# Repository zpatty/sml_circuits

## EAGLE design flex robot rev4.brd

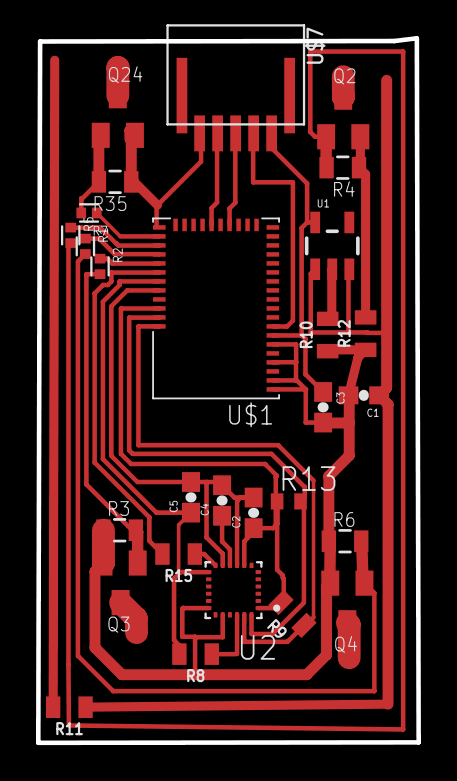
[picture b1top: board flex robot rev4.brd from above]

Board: 2 copper layers, 21.1 x 39.1 mm, 28 parts (0 on the bottom side), 25 nets.

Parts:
C1, C2, C4, C5: 1; 0603-CAP
C3: 0603-CAP
Q2, Q3, Q4, Q24: AO3400A; SOT23
R1, R2, R5, R7: ERA-2AED102X; RESC1005X40
R3, R4, R6, R35: 22.5kΩ; 0805
R8, R9, R10, R11, R12, R15: 0.22; 0805
R13: R0402
U1: TC7SU04F; SOT23-5
U2: MPU-9250; QFN40P300X300X105-25N
U$1: RFD77101
U$7: CON_01X05; HFW6R-2STE1LF

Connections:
GND: C1.2, C3.2, Q3.2, Q4.2, Q24.2, R3.1, R6.1, R10.1, R12.1, R35.1, U2.18, U2.20, U$1.1, U$1.2, U$1.4, U$1.6, U$1.19, U$1.30, U$7.5
unnamed: U$1.8, U$7.2
unnamed: C1.1, R11.1, U1.1, U1.3
unnamed: R1.1, U$1.33
unnamed: Q3.1, R2.2, R3.2
unnamed: U$1.23, U$7.3
unnamed: C4.1, U2.10
unnamed: U$1.25, U$7.4
unnamed: C2.2, C4.2, C5.2, U2.9, U2.11, U$1.37
unnamed: R5.1, U$1.32
unnamed: R7.1, U$1.31
unnamed: Q2.1, R4.2, R5.2
unnamed: Q4.1, R1.2, R6.2
unnamed: Q2.2, R4.1, R12.2
unnamed: C5.1, R8.2, U2.13, U$1.36
unnamed: C3.1, U1.5, U$1.7, U$7.1
unnamed: C2.1, R9.2, R13.1, U2.1, U2.8, U$1.39
unnamed: R9.1, U2.23, U$1.41
unnamed: R13.2, U2.24, U$1.40
unnamed: R8.1, U2.22
unnamed: R15.1, U2.12
unnamed: R15.2, U$1.35
unnamed: R10.2, U1.2
unnamed: R2.1, U$1.34
unnamed: Q24.1, R7.2, R35.2

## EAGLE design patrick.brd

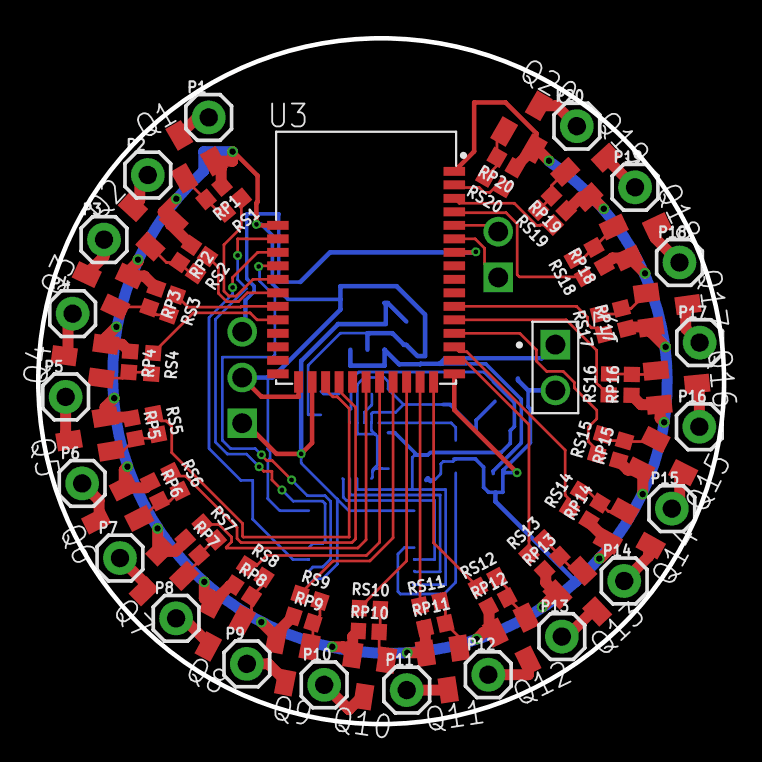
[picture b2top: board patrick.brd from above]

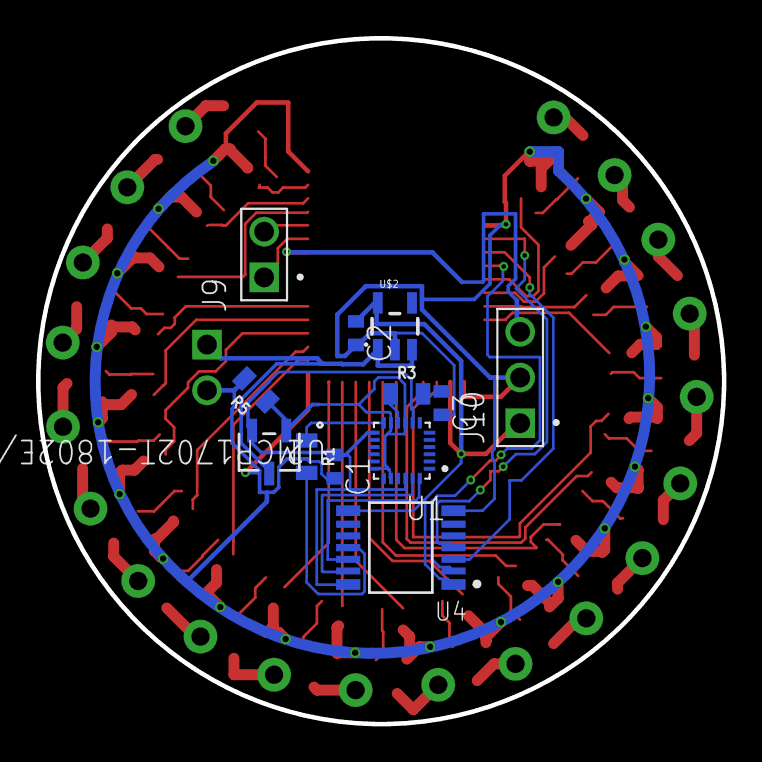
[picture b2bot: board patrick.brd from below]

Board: 2 copper layers, 38.1 x 38.1 mm, 94 parts (12 on the bottom side), 77 nets.

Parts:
C1, C2, C3: C0402
J7, J9: 61300211121
J10: 61300311121
P1, P2, P3, P4, P5, P6, P7, P8, P9, P10, P11, P12, P13, P14, P15, P16, P17, P18, P19, P20: 1X01
Q1, Q2, Q3, Q4, Q5, Q6, Q7, Q8, Q9, Q10, Q11, Q12, Q13, Q14, Q15, Q16, Q17, Q18, Q19, Q20: SOT23
R1, R3, R5: 0805
RP1, RP2, RP3, RP4, RP5, RP6, RP7, RP8, RP9, RP10, RP11, RP12, RP13, RP14, RP15, RP16, RP17, RP18, RP19, RP20: 0402
RS1, RS2, RS3, RS4, RS5, RS6, RS7, RS8, RS9, RS10, RS11, RS12, RS13, RS14, RS15, RS16, RS17, RS18, RS19, RS20: 0402
U1: ICM-20948; QFN40P300X300X105-24N
U2: MCP1702T-1802E/CB; SOT-23A_MC
U3: BL652-SA-01; XCVR_BL652-SA-01
U4: NXP_NTS0104PW,118NXP_NTS0104PW,118_0_3; NXP_NTS0104PW,118_3
U$2: SPX3819M5_3_3; SOT23-5

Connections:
+1.8V: C1.1, U1.8, U1.13, U1.22, U2.2, U4.14
+3V: C2.1, J10.1, U3.26, U4.1, U4.8, U$2.5
GND: C1.2, C2.2, C3.2, J7.2, J10.2, Q1.2, Q2.2, Q3.2, Q4.2, Q5.2, Q6.2, Q7.2, Q8.2, Q9.2, Q10.2, Q11.2, Q12.2, Q13.2, Q14.2, Q15.2, Q16.2, Q17.2, Q18.2, Q19.2, Q20.2, R5.2, RP1.1, RP2.1, RP3.1, RP4.1, RP5.1, RP6.1, RP7.1, RP8.1, RP9.1, RP10.1, RP11.1, RP12.1, RP13.1, RP14.1, RP15.1, RP16.1, RP17.1, RP18.1, RP19.1, RP20.1, U3.1, U3.16, U3.27, U3.39, U4.7, U$2.2
GND1: R5.1, U1.9, U1.11, U1.18, U1.20, U2.1
INT_A: U3.38, U4.4
INT_B: R1.2, U4.11
unnamed: R3.1, U1.10
unnamed: C3.1, R3.2
unnamed: R1.1, U1.12
unnamed: Q1.1, RP1.2, RS1.2
unnamed: Q2.1, RP2.2, RS2.2
unnamed: Q3.1, RP3.2, RS3.2
unnamed: Q4.1, RP4.2, RS4.2
unnamed: Q5.1, RP5.2, RS5.2
unnamed: Q6.1, RP6.2, RS6.2
unnamed: Q7.1, RP7.2, RS7.2
unnamed: Q8.1, RP8.2, RS8.2
unnamed: Q9.1, RP9.2, RS9.2
unnamed: Q10.1, RP10.2, RS10.2
unnamed: Q11.1, RP11.2, RS11.2
unnamed: Q12.1, RP12.2, RS12.2
unnamed: Q13.1, RP13.2, RS13.2
unnamed: Q14.1, RP14.2, RS14.2
unnamed: Q15.1, RP15.2, RS15.2
unnamed: Q16.1, RP16.2, RS16.2
unnamed: Q17.1, RP17.2, RS17.2
unnamed: Q18.1, RP18.2, RS18.2
unnamed: Q19.1, RP19.2, RS19.2
unnamed: Q20.1, RP20.2, RS20.2
RESET: J10.3, U3.7
SCL_A: U3.36, U4.2
SCL_B: U1.23, U4.13
SDA_A: U3.37, U4.3
SDA_B: U1.24, U4.12
SMA1_PWR: P1.1, Q1.3
SMA1_SIG: RS1.1, U3.35
SMA2_PWR: P2.1, Q2.3
SMA2_SIG: RS2.1, U3.34
SMA3_PWR: P3.1, Q3.3
SMA3_SIG: RS3.1, U3.33
SMA4_PWR: P4.1, Q4.3
SMA4_SIG: RS4.1, U3.32
SMA5_PWR: P5.1, Q5.3
SMA5_SIG: RS5.1, U3.25
SMA6_PWR: P6.1, Q6.3
SMA6_SIG: RS6.1, U3.24
SMA7_PWR: P7.1, Q7.3
SMA7_SIG: RS7.1, U3.22
SMA8_PWR: P8.1, Q8.3
SMA8_SIG: RS8.1, U3.21
SMA9_PWR: P9.1, Q9.3
SMA9_SIG: RS9.1, U3.20
SMA10_PWR: P10.1, Q10.3
SMA10_SIG: RS10.1, U3.19
SMA11_PWR: P11.1, Q11.3
SMA11_SIG: RS11.1, U3.18
SMA12_PWR: P12.1, Q12.3
SMA12_SIG: RS12.1, U3.17
SMA13_PWR: P13.1, Q13.3
SMA13_SIG: RS13.1, U3.15
SMA14_PWR: P14.1, Q14.3
SMA14_SIG: RS14.1, U3.14
SMA15_PWR: P15.1, Q15.3
SMA15_SIG: RS15.1, U3.13
SMA16_PWR: P16.1, Q16.3
SMA16_SIG: RS16.1, U3.12
SMA17_PWR: P17.1, Q17.3
SMA17_SIG: RS17.1, U3.11
SMA18_PWR: P18.1, Q18.3
SMA18_SIG: RS18.1, U3.4
SMA19_PWR: P19.1, Q19.3
SMA19_SIG: RS19.1, U3.3
SMA20_PWR: P20.1, Q20.3
SMA20_SIG: RS20.1, U3.2
SWDCLK: J9.1, U3.6
SWDIO: J9.2, U3.5
VBAT_1: J7.1, U2.3, U$2.1, U$2.3

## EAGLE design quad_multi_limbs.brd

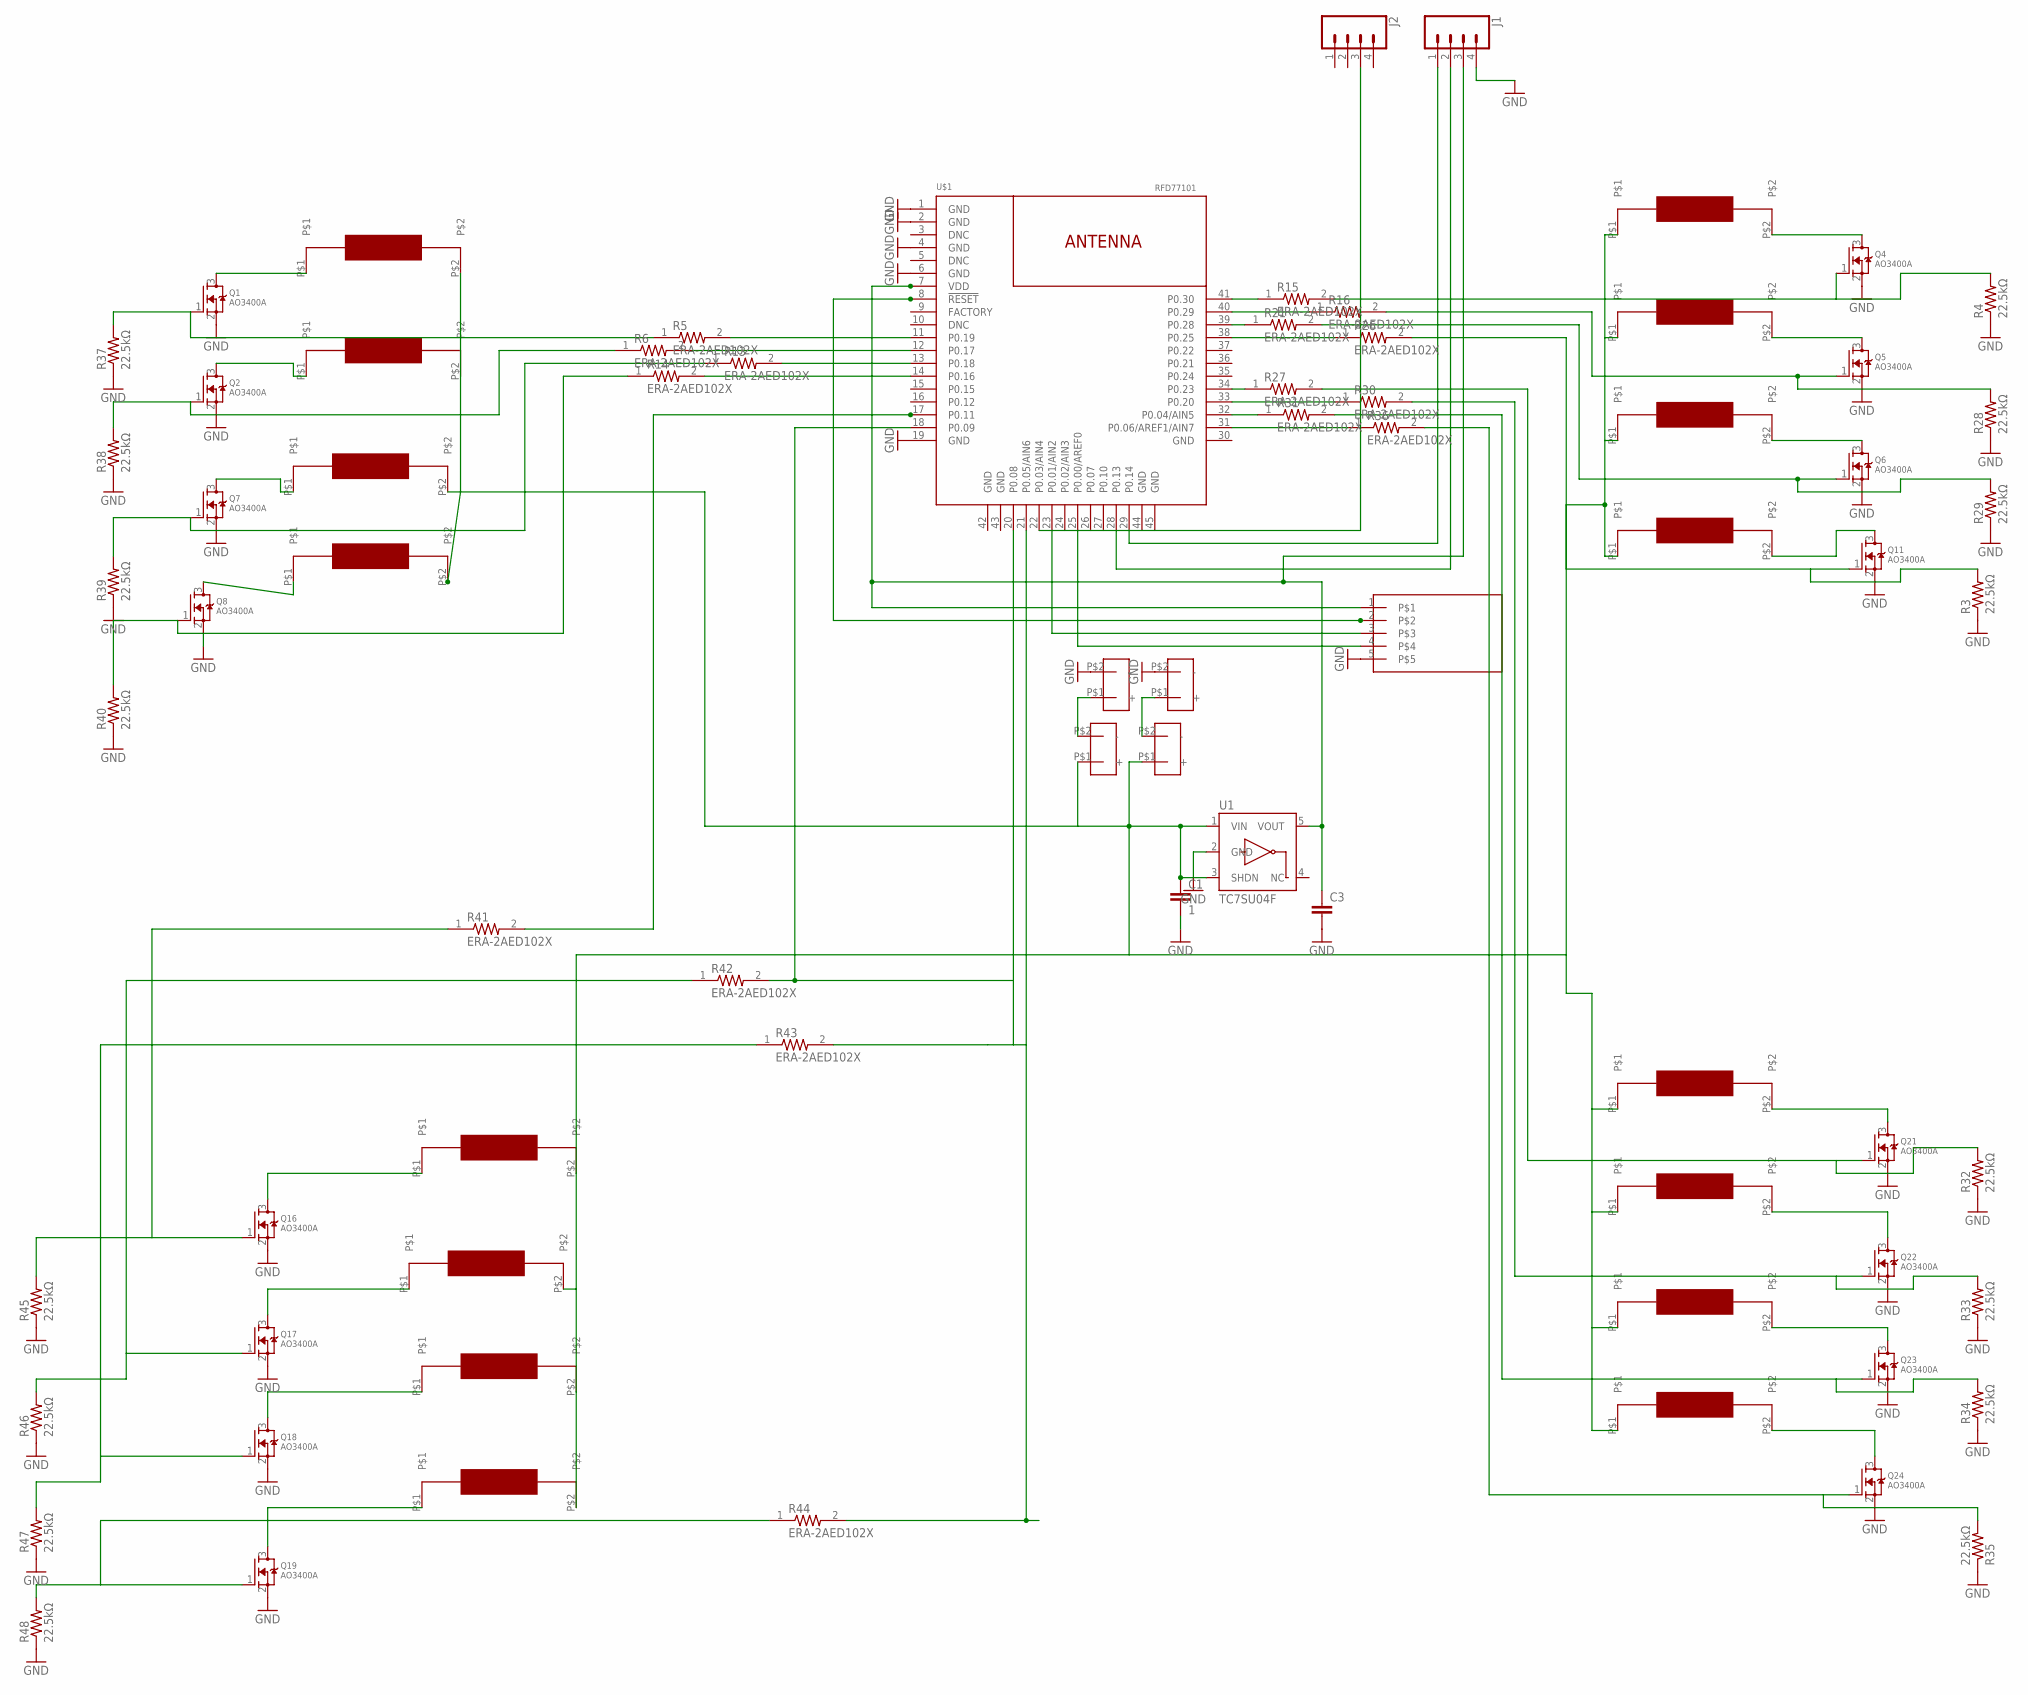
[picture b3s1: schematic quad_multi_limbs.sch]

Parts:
C1: 1; 0603-CAP
C3: CAP0603-CAP; 0603-CAP
J1, J2: CONN_04POLAR; MOLEX-1X4
Q1, Q2, Q4, Q5, Q6, Q7, Q8, Q11, Q16, Q17, Q18, Q19, Q21, Q22, Q23, Q24: AO3400A; SOT23
R1, R2, R7, R8, R9, R10, R11, R12, R17, R18, R19, R20, R22, R23, R24, R25: QUADWALKING; MULTI_QUAD_ACTUATOR
R3, R4, R28, R29, R32, R33, R34, R35, R37, R38, R39, R40, R45, R46, R47, R48: 22.5kΩ; 0805
R5, R6, R13, R14, R15, R16, R21, R26, R27, R30, R31, R36, R41, R42, R43, R44: ERA-2AED102X; RESC1005X40
U1: TC7SU04F; SOT23-5
U$1: RFD77101
U$2, U$3, U$11, U$12: MOLEX-053261; MOLEX-05326
U$7: CON_01X05; HFW6R-2STE1LF

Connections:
GND: C1.2, C3.2, J1.4, Q1.2 (S), Q2.2 (S), Q4.2 (S), Q5.2 (S), Q6.2 (S), Q7.2 (S), Q8.2 (S), Q11.2 (S), Q16.2 (S), Q17.2 (S), Q18.2 (S), Q19.2 (S), Q21.2 (S), Q22.2 (S), Q23.2 (S), Q24.2 (S), R3.1, R4.1, R28.1, R29.1, R32.1, R33.1, R34.1, R35.1, R37.1, R38.1, R39.1, R40.1, R45.1, R46.1, R47.1, R48.1, U1.2 (GND), U$1.1 (GND), U$1.2 (GND), U$1.4 (GND), U$1.6 (GND), U$1.19 (GND), U$1.30 (GND), U$1.42 (GND), U$1.43 (GND), U$1.44 (GND), U$1.45 (GND), U$2.P$2 (-), U$7.5, U$11.P$2 (-)
unnamed: U$1.8 (!RESET!), U$7.2
unnamed: C1.1, R1.P$1, R2.P$1, R7.P$1, R8.P$1, R9.P$2, R10.P$2, R11.P$2, R12.P$2, R17.P$2, R18.P$2, R19.P$2, R20.P$2, R22.P$1, R23.P$1, R24.P$1, R25.P$1, U1.1 (VIN), U1.3 (SHDN), U$3.P$1 (+), U$12.P$1 (+)
unnamed: U$11.P$1 (+), U$12.P$2 (-)
unnamed: Q4.1 (G), R4.2, R15.2
unnamed: U$1.23 (P0.01/AIN2), U$7.3
unnamed: C3.1, J1.3, U1.5 (VOUT), U$1.7 (VDD), U$7.1
unnamed: Q5.1 (G), R16.2, R28.2
unnamed: Q6.1 (G), R21.2, R29.2
unnamed: U$1.25 (P0.00/AREF0), U$7.4
unnamed: Q11.1 (G), R3.2, R26.2
unnamed: Q1.3 (D), R9.P$1
unnamed: U$2.P$1 (+), U$3.P$2 (-)
unnamed: J1.1, U$1.29 (P0.14)
unnamed: J1.2, U$1.28 (P0.13)
unnamed: R5.2, U$1.11 (P0.19)
unnamed: R6.2, U$1.12 (P0.17)
unnamed: Q2.3 (D), R10.P$1
unnamed: Q7.3 (D), R11.P$1
unnamed: Q8.3 (D), R12.P$1
unnamed: R13.2, U$1.13 (P0.18)
unnamed: R14.2, U$1.14 (P0.16)
unnamed: Q1.1 (G), R5.1, R37.2
unnamed: Q2.1 (G), R6.1, R38.2
unnamed: Q7.1 (G), R13.1, R39.2
unnamed: Q8.1 (G), R14.1, R40.2
unnamed: R15.1, U$1.41 (P0.30)
unnamed: R16.1, U$1.40 (P0.29)
unnamed: Q16.3 (D), R17.P$1
unnamed: Q17.3 (D), R18.P$1
unnamed: Q18.3 (D), R19.P$1
unnamed: Q19.3 (D), R20.P$1
unnamed: R21.1, U$1.39 (P0.28)
unnamed: R26.1, U$1.38 (P0.25)
unnamed: R41.2, U$1.17 (P0.11)
unnamed: Q17.1 (G), R42.1, R46.2
unnamed: Q18.1 (G), R43.1, R47.2
unnamed: R44.2, U$1.21 (P0.05/AIN6)
unnamed: Q4.3 (D), R8.P$2
unnamed: Q5.3 (D), R7.P$2
unnamed: Q6.3 (D), R2.P$2
unnamed: Q11.3 (D), R1.P$2
unnamed: R27.1, U$1.34 (P0.23)
unnamed: R30.1, U$1.33 (P0.20)
unnamed: R31.1, U$1.32 (P0.04/AIN5)
unnamed: Q21.3 (D), R22.P$2
unnamed: Q22.3 (D), R23.P$2
unnamed: Q23.3 (D), R24.P$2
unnamed: Q24.3 (D), R25.P$2
unnamed: R36.1, U$1.31 (P0.06/AREF1/AIN7)
unnamed: Q16.1 (G), R41.1, R45.2
unnamed: Q21.1 (G), R27.2, R32.2
unnamed: Q22.1 (G), R30.2, R33.2
unnamed: Q23.1 (G), R31.2, R34.2
unnamed: Q24.1 (G), R35.2, R36.2
unnamed: R42.2, U$1.18 (P0.09)
unnamed: R43.2, U$1.20 (P0.08)
unnamed: Q19.1 (G), R44.1, R48.2
unnamed: J2.3, U$1.22 (P0.03/AIN4)

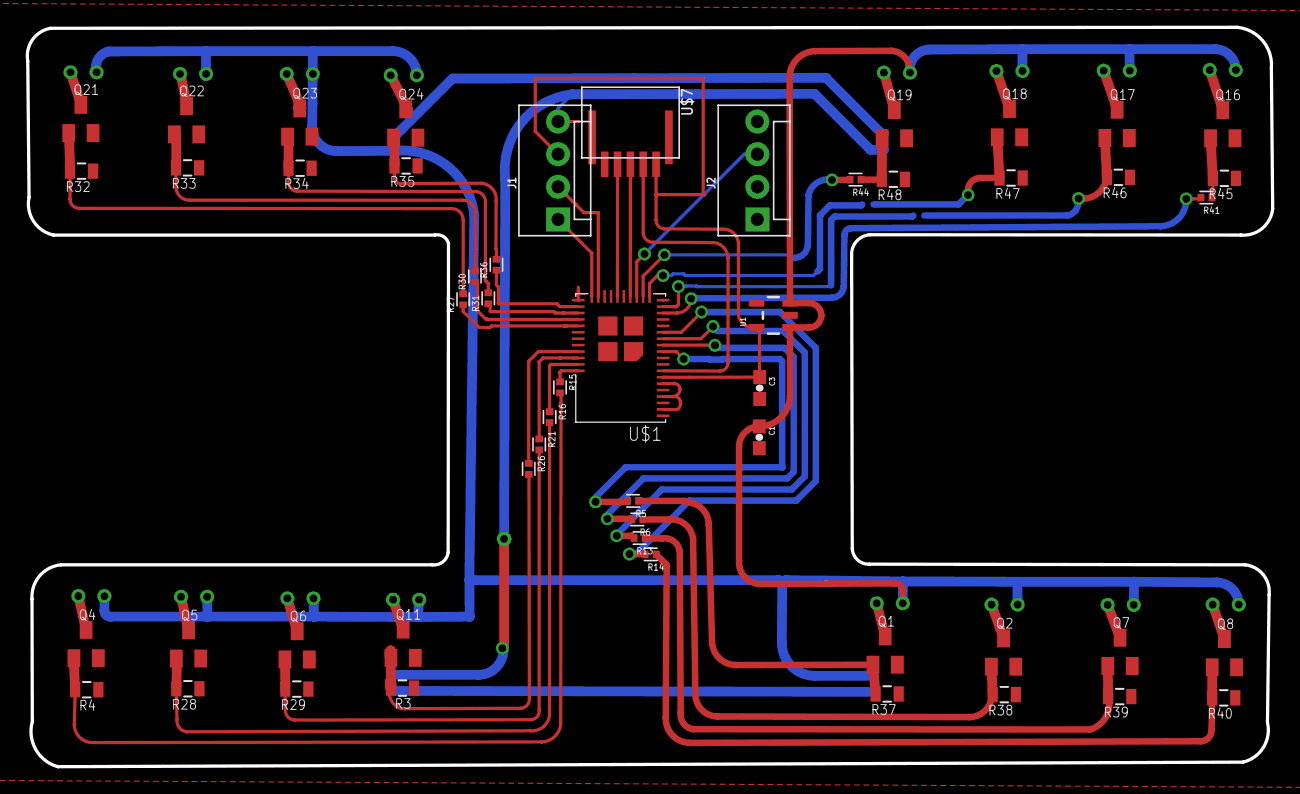
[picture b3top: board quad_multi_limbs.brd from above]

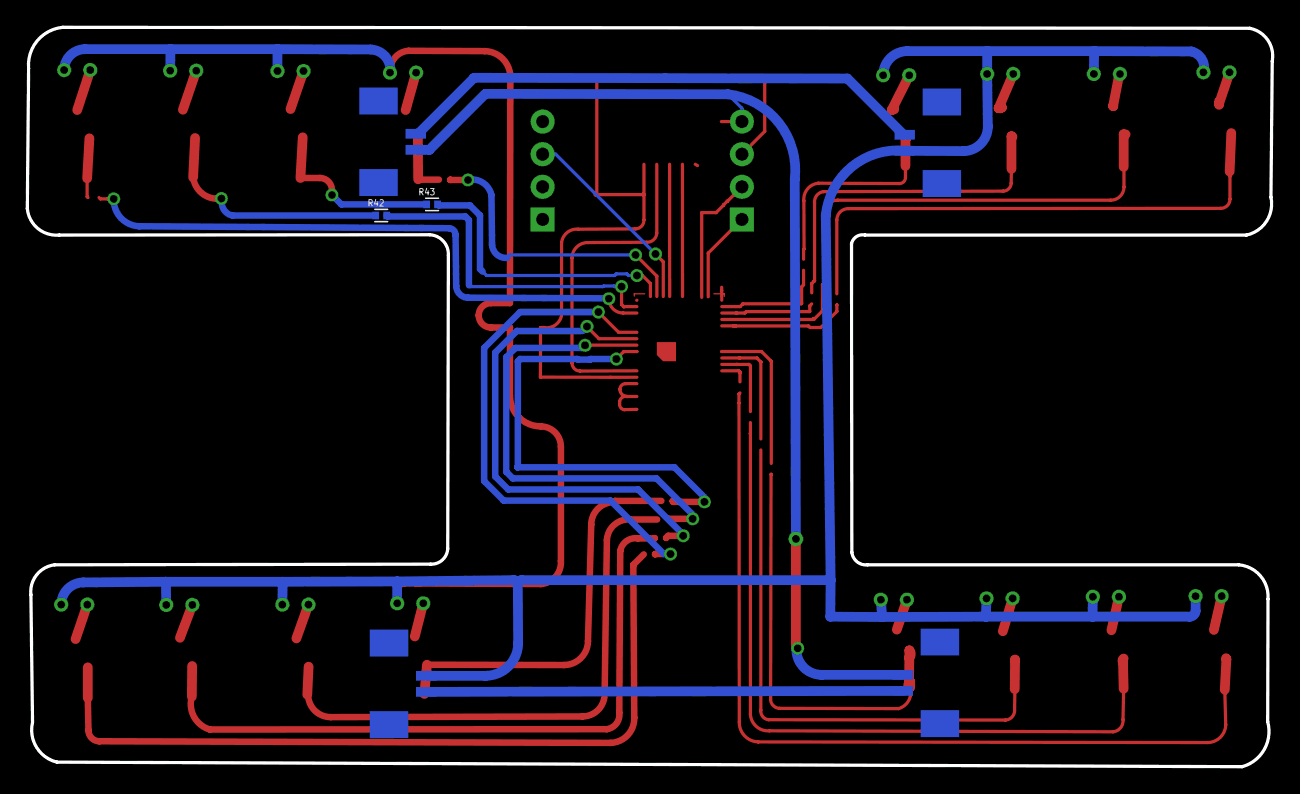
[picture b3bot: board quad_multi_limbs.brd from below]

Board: 2 copper layers, 97.0 x 57.6 mm, 75 parts (7 on the bottom side), 59 nets.

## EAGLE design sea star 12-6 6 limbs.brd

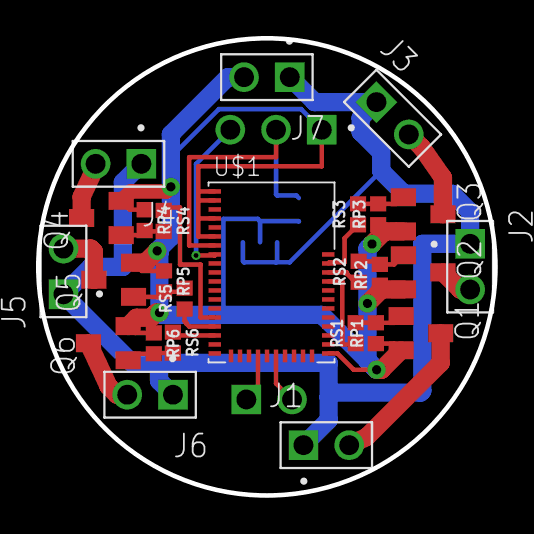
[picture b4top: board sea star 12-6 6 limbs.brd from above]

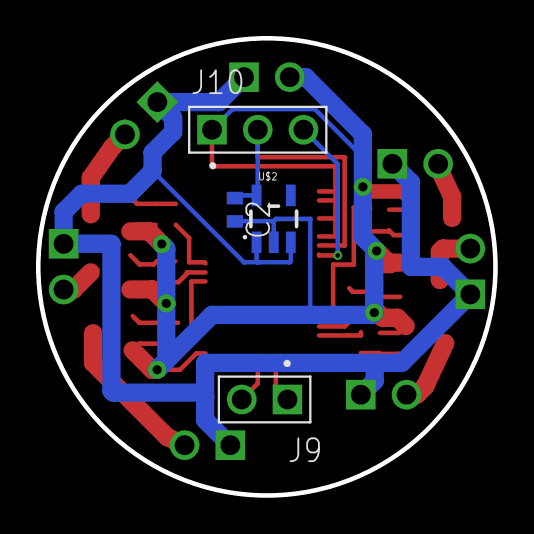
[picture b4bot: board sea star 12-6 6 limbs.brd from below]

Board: 2 copper layers, 25.4 x 25.4 mm, 30 parts (4 on the bottom side), 24 nets.

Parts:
C2: C0402
J1, J2, J3, J4, J5, J6, J7, J9: 61300211121
J10: 61300311121
Q1, Q2, Q3, Q4, Q5, Q6: SOT23
RP1, RP2, RP3, RP4, RP5, RP6: 0402
RS1, RS2, RS3, RS4, RS5, RS6: 0402
U$1: RFD77101
U$2: SPX3819M5_3_3; SOT23-5

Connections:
+3V: C2.1, J10.2, U$1.7, U$2.5
GND: C2.2, J7.2, J10.1, Q1.2, Q2.2, Q3.2, Q4.2, Q5.2, Q6.2, RP1.1, RP2.1, RP3.1, RP4.1, RP5.1, RP6.1, U$1.1, U$1.2, U$1.4, U$1.6, U$1.19, U$1.30, U$2.2
GPIO0: J9.2, U$1.25
GPIO1: J9.1, U$1.23
unnamed: Q1.1, RP1.2, RS1.2
unnamed: Q2.1, RP2.2, RS2.2
unnamed: Q3.1, RP3.2, RS3.2
unnamed: Q4.1, RP4.2, RS4.2
unnamed: Q5.1, RP5.2, RS5.2
unnamed: Q6.1, RP6.2, RS6.2
RESET: J10.3, U$1.8
SMA1_PWR: J1.2, Q1.3
SMA1_SIG: RS1.1, U$1.38
SMA2_PWR: J2.2, Q2.3
SMA2_SIG: RS2.1, U$1.39
SMA3_PWR: J3.2, Q3.3
SMA3_SIG: RS3.1, U$1.40
SMA4_PWR: J4.2, Q4.3
SMA4_SIG: RS4.1, U$1.15
SMA5_PWR: J5.2, Q5.3
SMA5_SIG: RS5.1, U$1.16
SMA6_PWR: J6.2, Q6.3
SMA6_SIG: RS6.1, U$1.17
VBAT_1: J1.1, J2.1, J3.1, J4.1, J5.1, J6.1, J7.1, U$2.1, U$2.3

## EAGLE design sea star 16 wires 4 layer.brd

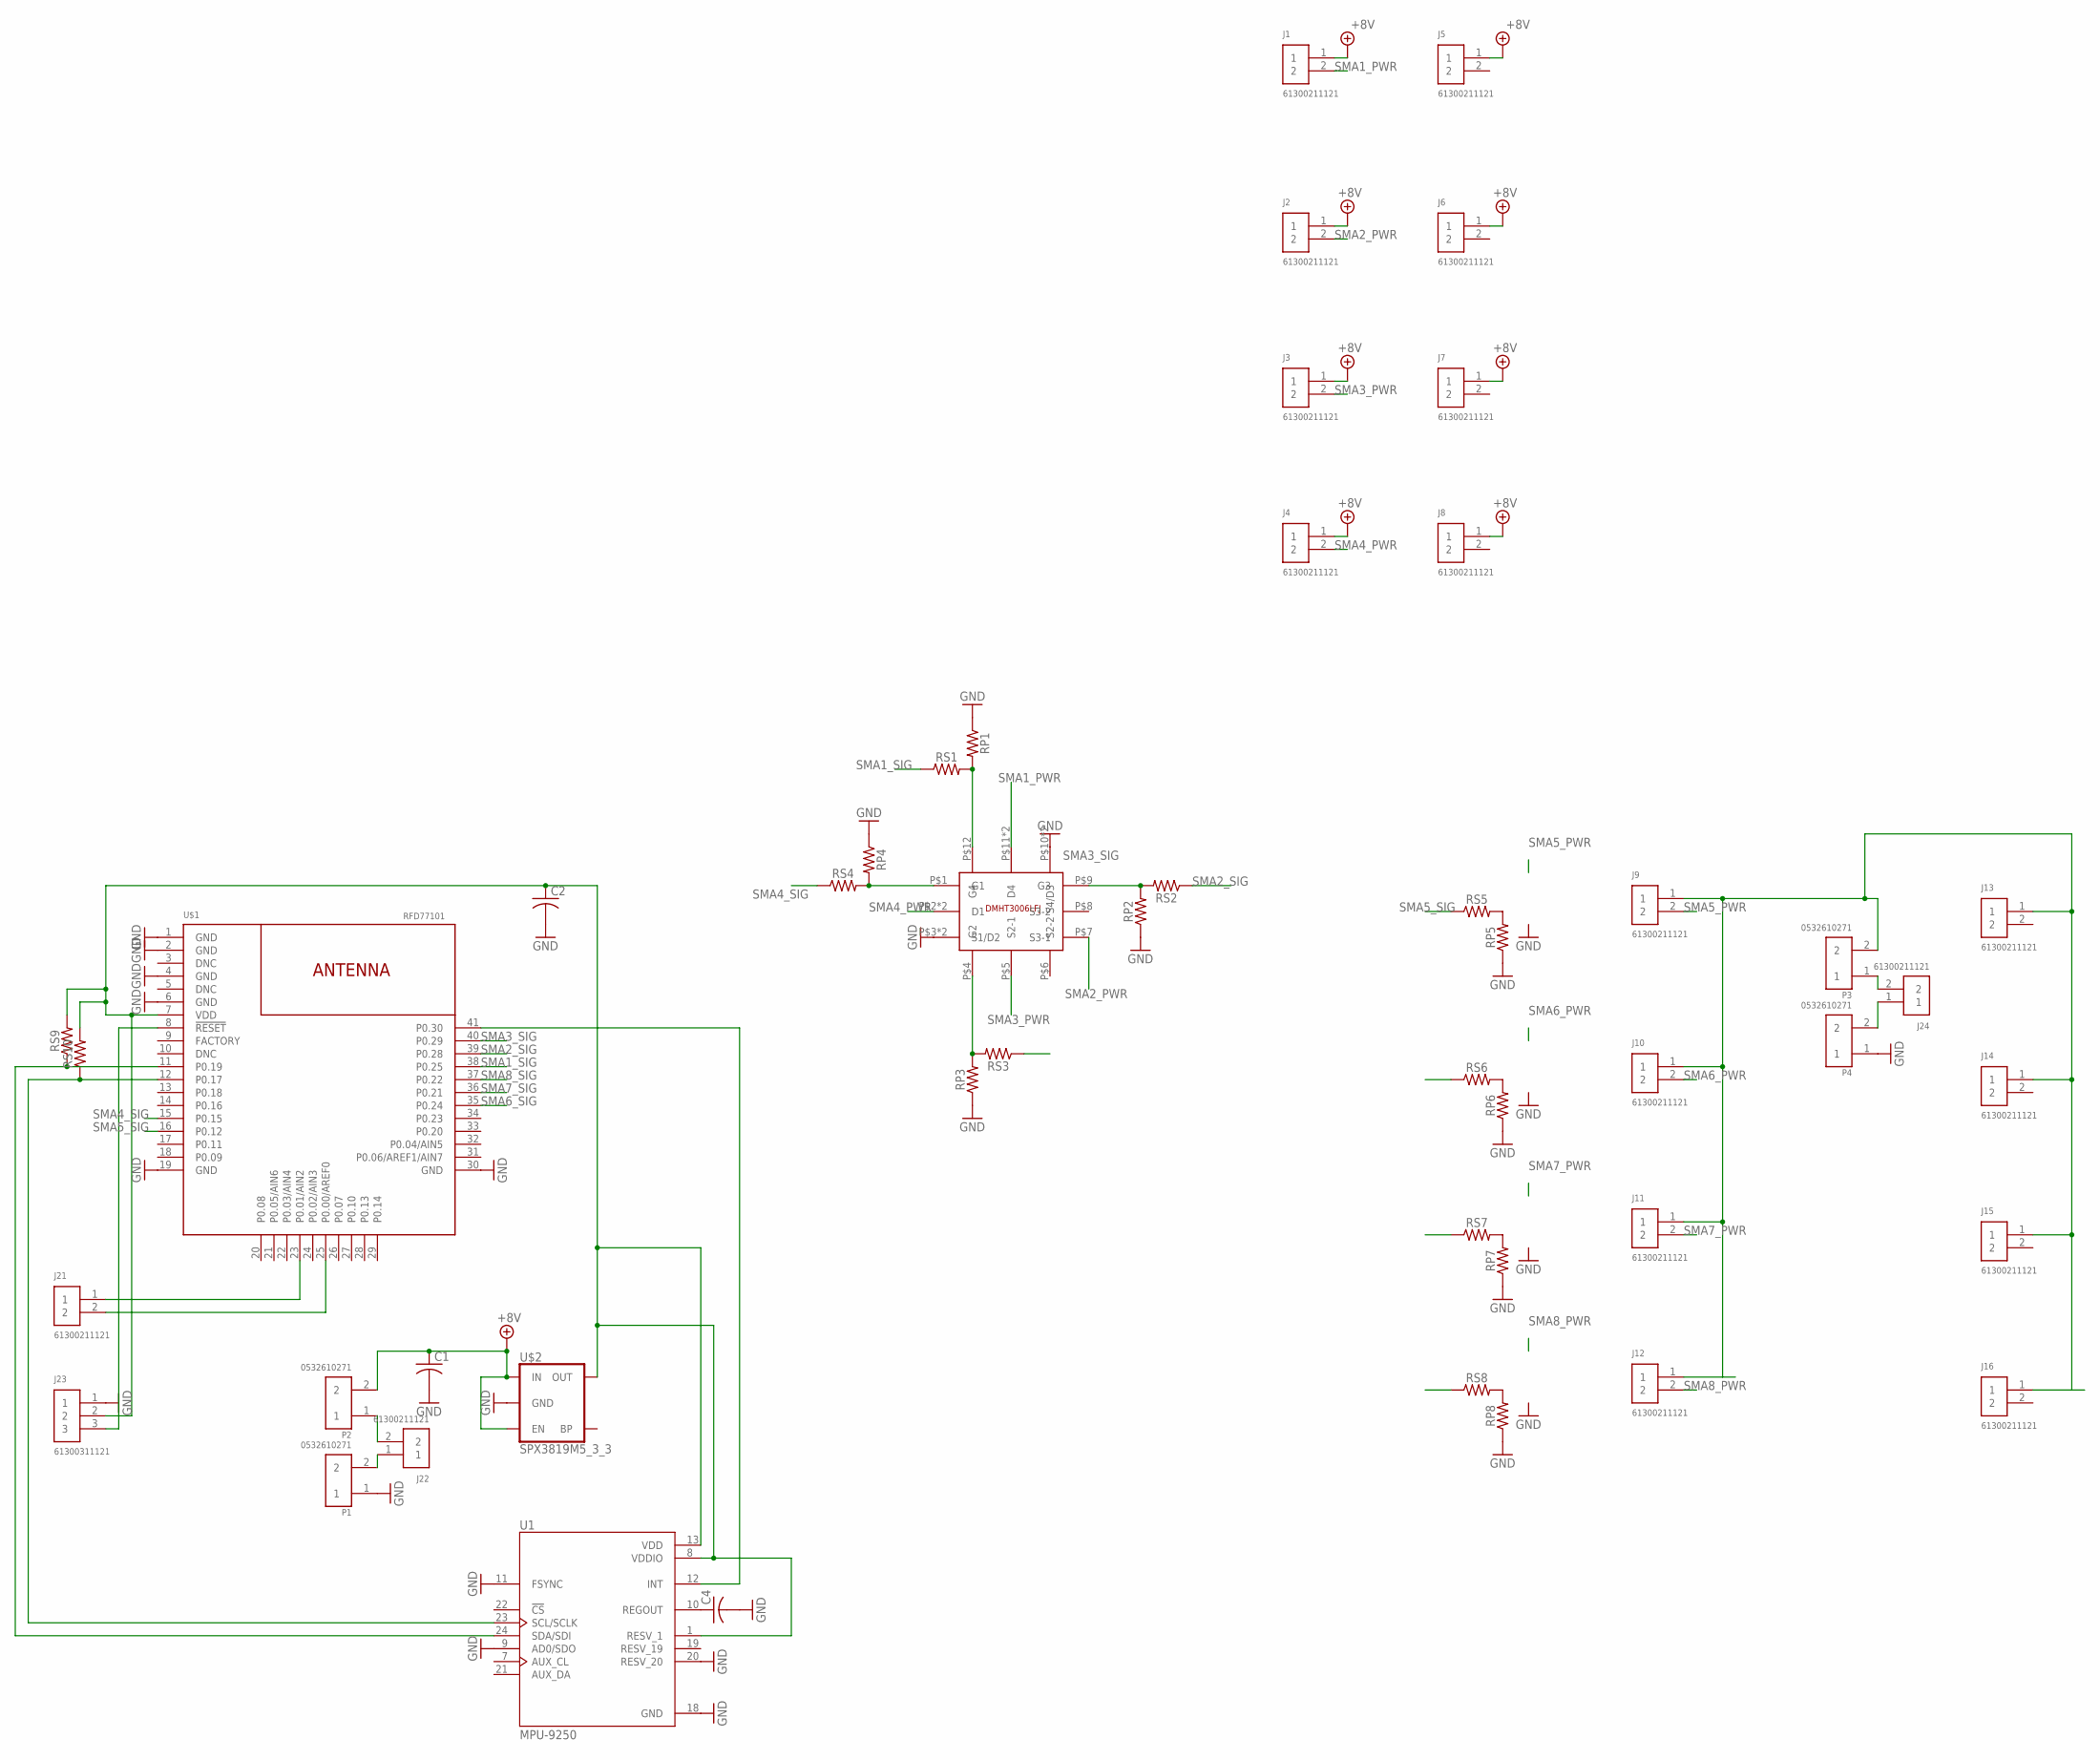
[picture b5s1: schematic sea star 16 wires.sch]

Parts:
C1, C2, C4: C-USC0402; C0402
J1, J2, J3, J4, J5, J6, J7, J8, J9, J10, J11, J12, J13, J14, J15, J16, J21, J22, J24: 61300211121
J23: 61300311121
P1, P2, P3, P4: 0532610271; MOLEX_0532610271
RP1, RP2, RP3, RP4, RP5, RP6, RP7, RP8: 0402
RS1, RS2, RS3, RS4, RS5, RS6, RS7, RS8, RS9, RS10: 0402
U1: MPU-9250; QFN40P300X300X105-24N
U$1: RFD77101
U$2: SPX3819M5_3_3; SOT23-5
U$3: DMHT3006LFJ

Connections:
+3V: C2.1, J23.2, RS9.2, RS10.2, U1.1 (RESV_1), U1.8 (VDDIO), U1.13 (VDD), U$1.7 (VDD), U$2.5 (OUT)
GND: C1.2, C2.2, C4.2, J23.1, P1.1, P4.1, RP1.1, RP2.1, RP3.1, RP4.1, RP5.1, RP6.1, RP7.1, RP8.1, U1.9 (AD0/SDO), U1.11 (FSYNC), U1.18 (GND), U1.20 (RESV_20), U$1.1 (GND), U$1.2 (GND), U$1.4 (GND), U$1.6 (GND), U$1.19 (GND), U$1.30 (GND), U$2.2 (GND), U$3.P$3 (S1/D2), U$3.P$10 (S4/D3), U$3.P$14 (S4/D3), U$3.P$16 (S1/D2)
GPIO0: J21.2, U$1.25 (P0.00/AREF0)
GPIO1: J21.1, U$1.23 (P0.01/AIN2)
unnamed: RP1.2, RS1.2, U$3.P$12 (G4)
unnamed: RP3.2, RS3.2, U$3.P$4 (G2)
unnamed: RP4.2, RS4.2, U$3.P$1 (G1)
unnamed: RP5.2, RS5.2
unnamed: RP6.2, RS6.2
unnamed: RP7.2, RS7.2
unnamed: RP8.2, RS8.2
unnamed: C4.1, U1.10 (REGOUT)
unnamed: J22.2, P2.1
unnamed: J24.1, P4.2
unnamed: RS9.1, U1.24 (SDA/SDI), U$1.11 (P0.19)
unnamed: RS10.1, U1.23 (SCL/SCLK), U$1.12 (P0.17)
unnamed: U1.12 (INT), U$1.41 (P0.30)
unnamed: J24.2, P3.1
unnamed: J22.1, P1.2
unnamed: RP2.2, RS2.2, U$3.P$9 (G3)
unnamed: J9.1, J10.1, J11.1, J12.1, J13.1, J14.1, J15.1, J16.1, P3.2
RESET: J23.3, U$1.8 (!RESET!)
SMA1_PWR: J1.2, U$3.P$11 (D4), U$3.P$13 (D4)
SMA1_SIG: RS1.1, U$1.38 (P0.25)
SMA2_PWR: J2.2, U$3.P$7 (S3-1)
SMA2_SIG: RS2.1, U$1.39 (P0.28)
SMA3_PWR: J3.2, U$3.P$5 (S2-1)
SMA3_SIG: RS3.1, U$1.40 (P0.29)
SMA4_PWR: J4.2, U$3.P$2 (D1), U$3.P$15 (D1)
SMA4_SIG: RS4.1, U$1.15 (P0.15)
SMA5_PWR: J9.2
SMA5_SIG: RS5.1, U$1.16 (P0.12)
SMA6_PWR: J10.2
SMA6_SIG: RS6.1, U$1.35 (P0.24)
SMA7_PWR: J11.2
SMA7_SIG: RS7.1, U$1.36 (P0.21)
SMA8_PWR: J12.2
SMA8_SIG: RS8.1, U$1.37 (P0.22)
VBAT_1: C1.1, J1.1, J2.1, J3.1, J4.1, J5.1, J6.1, J7.1, J8.1, P2.2, U$2.1 (IN), U$2.3 (EN)

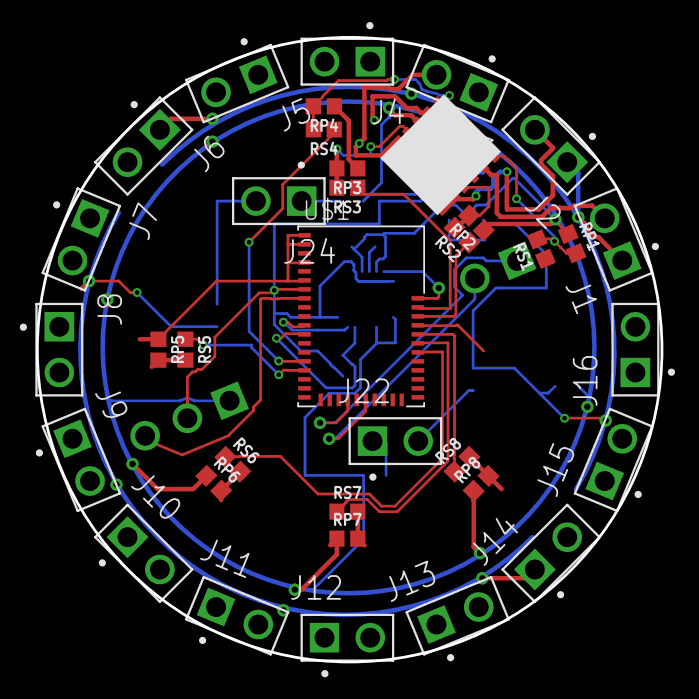
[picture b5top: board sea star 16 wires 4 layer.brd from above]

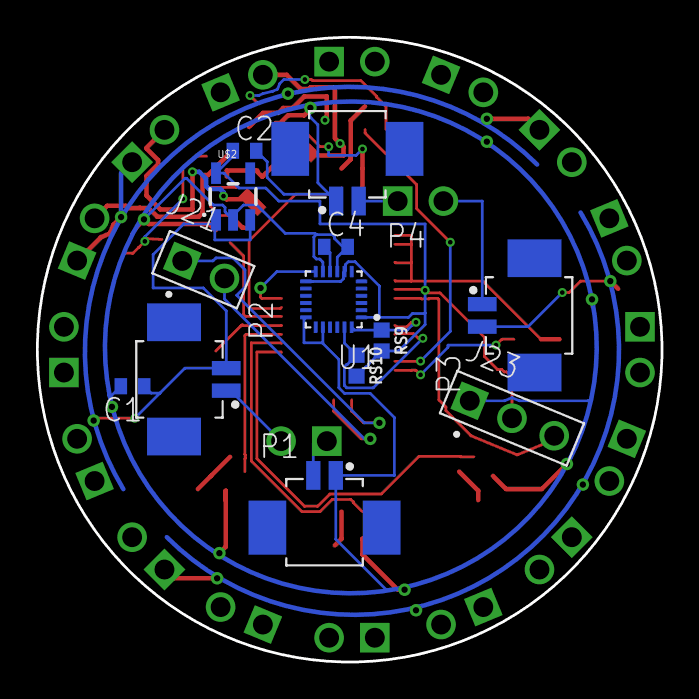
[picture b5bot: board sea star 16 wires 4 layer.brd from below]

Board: 2 copper layers, 34.7 x 34.7 mm, 49 parts (13 on the bottom side), 35 nets.

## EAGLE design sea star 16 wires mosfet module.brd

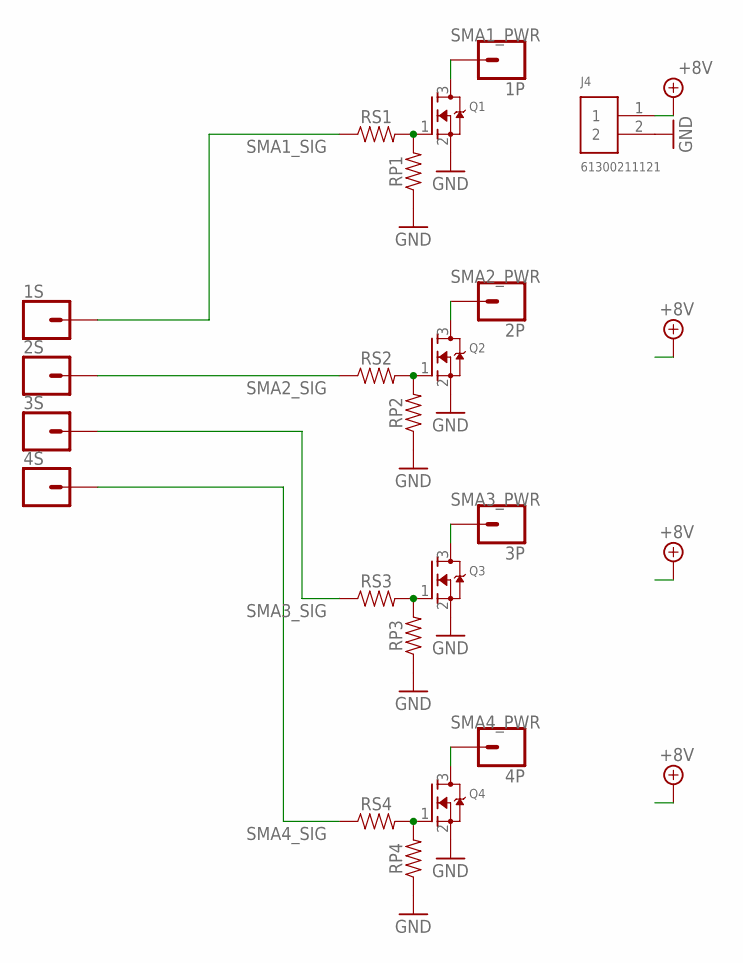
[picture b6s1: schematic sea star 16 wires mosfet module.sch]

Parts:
1P, 1S, 2P, 2S, 3P, 3S, 4P, 4S: CONN_01; 1X01
J4: 61300211121
Q1, Q2, Q3, Q4: MOSFET-NREFLOW; SOT23
RP1, RP2, RP3, RP4: 0402
RS1, RS2, RS3, RS4: 0402

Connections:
GND: J4.2, Q1.2 (S), Q2.2 (S), Q3.2 (S), Q4.2 (S), RP1.1, RP2.1, RP3.1, RP4.1
unnamed: Q1.1 (G), RP1.2, RS1.2
unnamed: Q2.1 (G), RP2.2, RS2.2
unnamed: Q3.1 (G), RP3.2, RS3.2
unnamed: Q4.1 (G), RP4.2, RS4.2
SMA1_PWR: 1P.1, Q1.3 (D)
SMA1_SIG: 1S.1, RS1.1
SMA2_PWR: 2P.1, Q2.3 (D)
SMA2_SIG: 2S.1, RS2.1
SMA3_PWR: 3P.1, Q3.3 (D)
SMA3_SIG: 3S.1, RS3.1
SMA4_PWR: 4P.1, Q4.3 (D)
SMA4_SIG: 4S.1, RS4.1
VBAT_1: J4.1

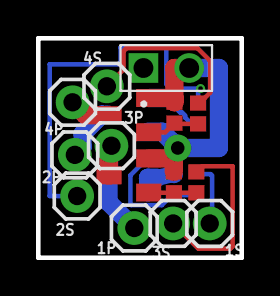
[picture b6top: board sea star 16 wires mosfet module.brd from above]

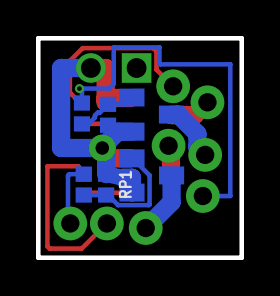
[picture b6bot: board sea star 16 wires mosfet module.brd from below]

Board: 2 copper layers, 11.3 x 12.2 mm, 21 parts (6 on the bottom side), 13 nets.

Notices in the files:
parts and their libraries:
SparkFun-Passives: Licensing: Creative Commons ShareAlike 4.0 International - https://creativecommons.org/licenses/by-sa/4.0
RFDigital: © 2015 RF Digital Corporation
COPYRIGHT: Copyright (C) 2018 Accelerated Designs. All rights reserved
